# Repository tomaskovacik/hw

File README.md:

repo for hw(pcbs mainly) part of electronic projects, sometimes there is also few software files here:)

kicad: projects made in kicad

audi_chorus_cd_changer_input: all files needed to convert audi chorus 1 to enable CD changer input, more: http://kovo-blog.blogspot.sk/2013/11/how-to-enable-cd-changer-input-on-audi.html

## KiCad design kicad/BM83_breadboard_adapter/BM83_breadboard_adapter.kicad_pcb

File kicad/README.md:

schematics and PCBs made in kicad

arduino based cdc emulator moved to https://github.com/tomaskovacik/vwcdavr/tree/master/HW/arduino_based_cdc_emulator

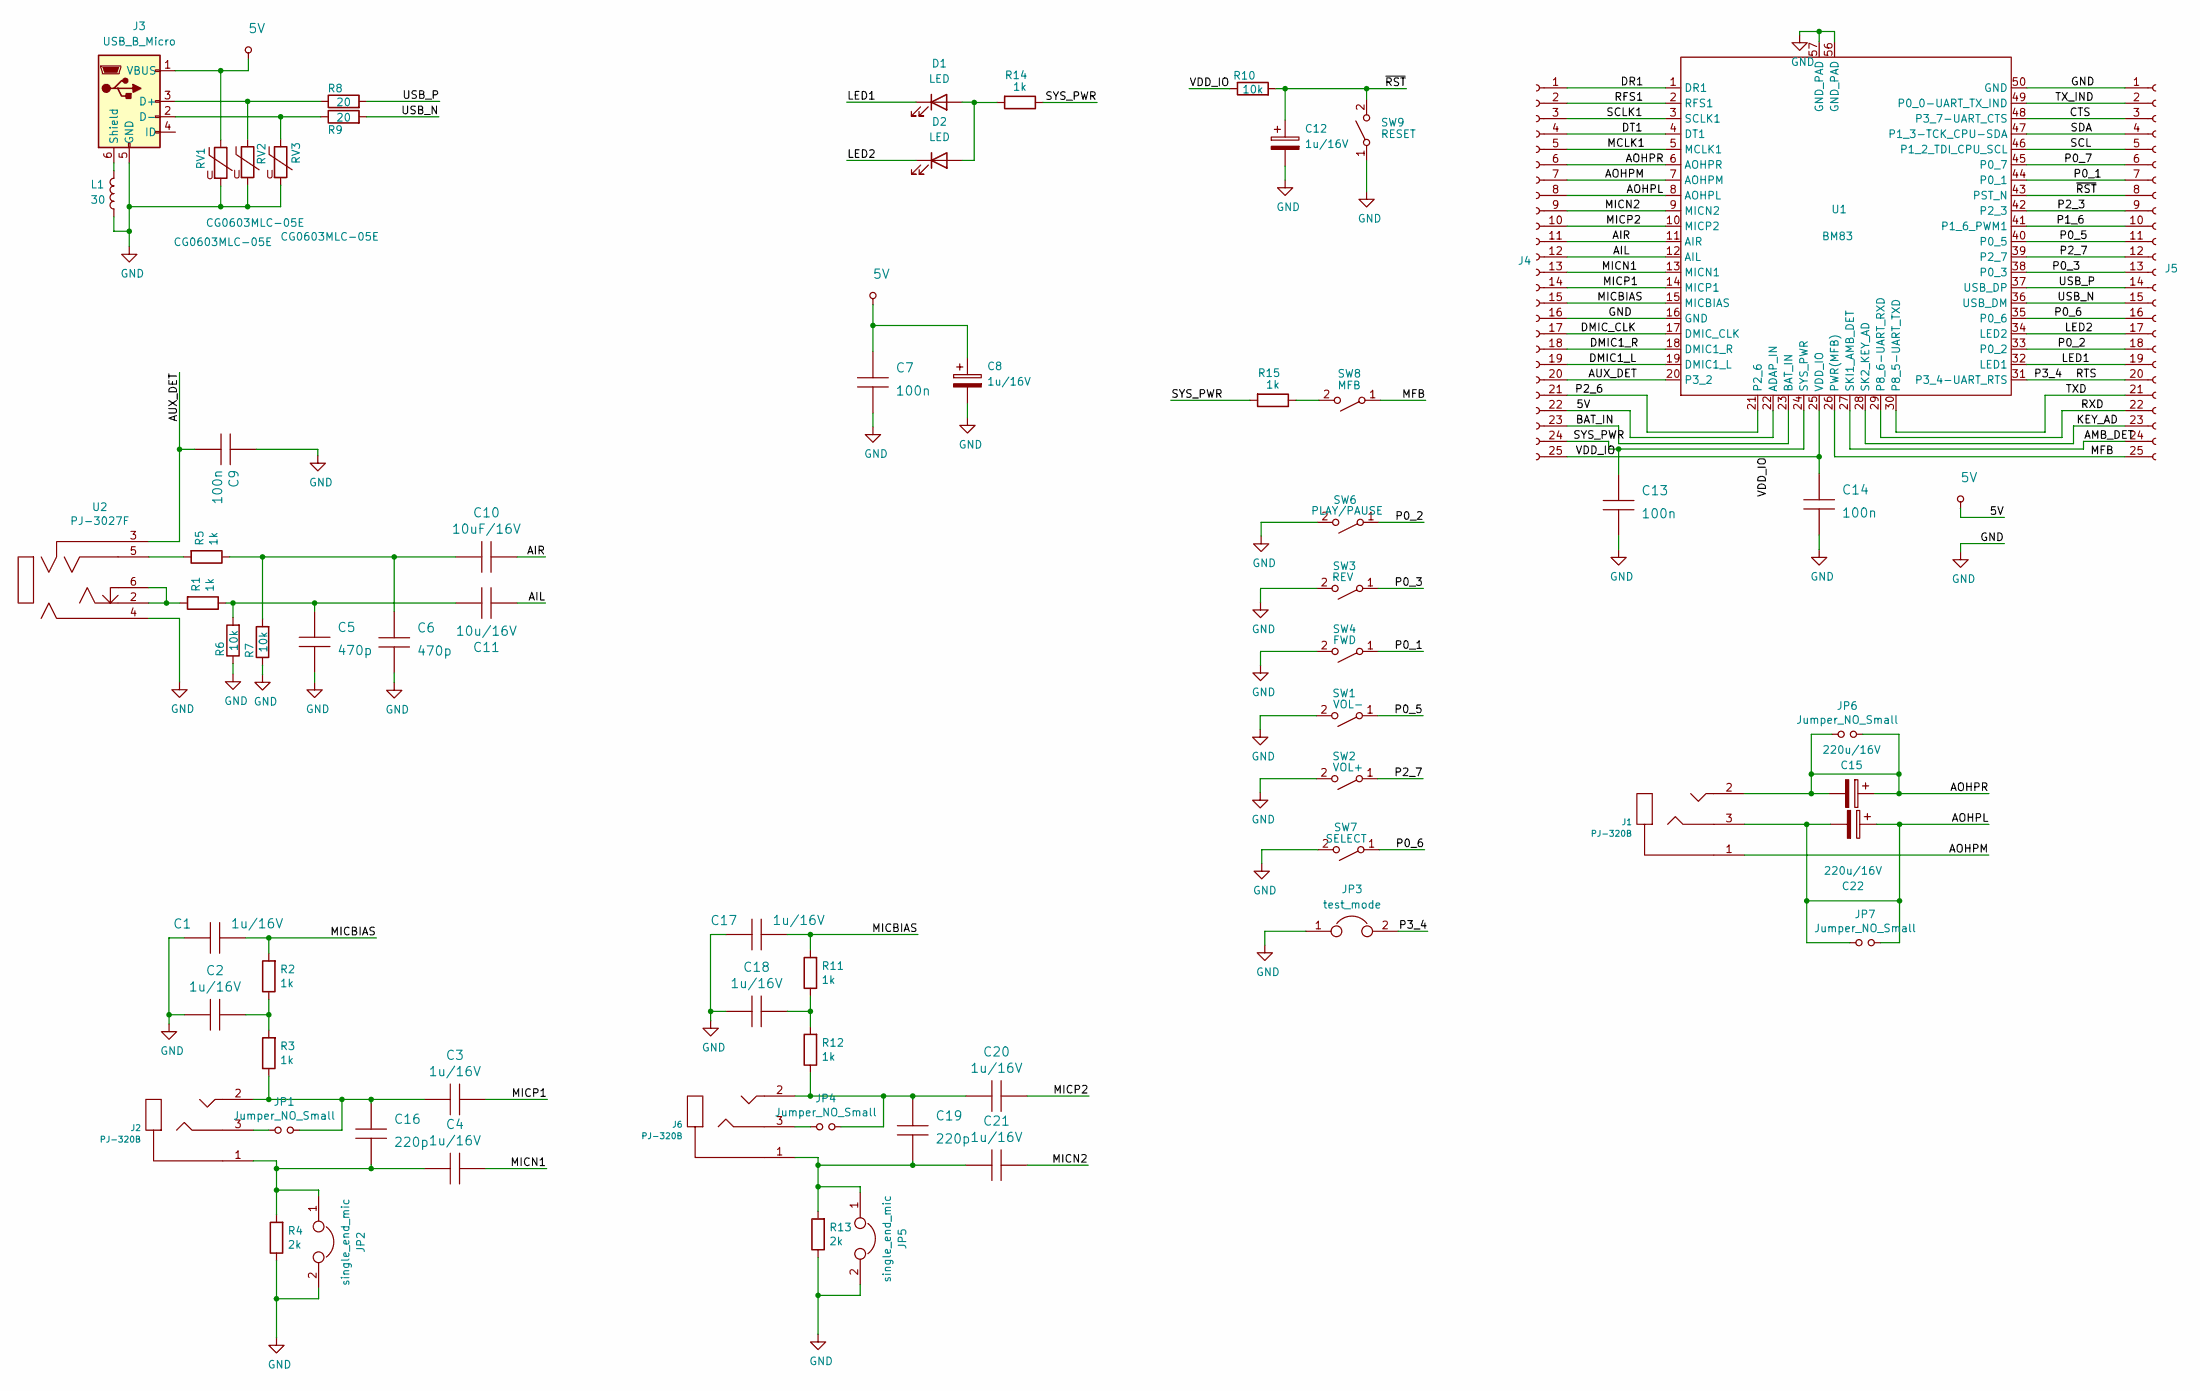
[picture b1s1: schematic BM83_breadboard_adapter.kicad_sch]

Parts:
C1, C2, C3, C4, C17, C18, C20, C21: 1u/16V; C_1206_HandSoldering
C5, C6: 470p; C_0805_HandSoldering
C7, C9, C13, C14: 100n; C_0805_HandSoldering
C8, C12: 1u/16V; TantalC_SizeA_EIA-3216_HandSoldering
C10: 10uF/16V; C_1206_HandSoldering
C11: 10u/16V; C_1206_HandSoldering
C15, C22: 220u/16V; C_Radial_D6.3_L11.2_P2.5
C16, C19: 220p; C_0805_HandSoldering
D1, D2: LED; LED_1206_HandSoldering
J1, J2, J6: PJ-320B; 3.5mm_stereo_jack_PJ320B
J3: USB_B_Micro; USB_Micro-B
J4, J5: Conn_01x25_Female; Pin_Header_Straight_1x25
JP1, JP4, JP6, JP7: Jumper_NO_Small; SolderJumper-2_P1.3mm_Open_RoundedPad1.0x1.5mm
JP2, JP5: single_end_mic; SolderJumper-2_P1.3mm_Open_RoundedPad1.0x1.5mm
JP3: test_mode; Pin_Header_Straight_1x02
L1: 30; R_1206_HandSoldering
R1, R2, R3, R5, R11, R12, R14, R15: 1k; R_0805_HandSoldering
R4, R13: 2k; R_0805_HandSoldering
R6, R7, R10: 10k; R_0805_HandSoldering
R8, R9: 20; R_0805_HandSoldering
RV1, RV2, RV3: CG0603MLC-05E; R_0603_HandSoldering
SW1: VOL-; SW_SPST_FSMSM
SW2: VOL+; SW_SPST_FSMSM
SW3: REV; SW_SPST_FSMSM
SW4: FWD; SW_SPST_FSMSM
SW6: PLAY/PAUSE; SW_SPST_FSMSM
SW7: SELECT; SW_SPST_FSMSM
SW8: MFB; SW_SPST_FSMSM
SW9: RESET; SW_SPST_FSMSM
U1: BM83
U2: PJ-3027F; PJ-327A

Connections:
5V: C7.1, C8.1, J3.1 (VBUS), J4.22, RV1.1, U1.22 (ADAP_IN)
/AIL: C11.2, J4.12, U1.12 (AIL)
/AIR: C10.1, J4.11, U1.11 (AIR)
/AMB_DET: J5.24, U1.27 (SKI1_AMB_DET)
/AOHPL: C22.1, C22.2, J1.3, J4.8, JP7.1, JP7.2, U1.8 (AOHPL)
/AOHPM: J1.1, J4.7, U1.7 (AOHPM)
/AOHPR: C15.1, C15.2, J1.2, J4.6, JP6.1, JP6.2, U1.6 (AOHPR)
/AUX_DET: C9.2, J4.20, U1.20 (P3_2), U2.3
/BAT_IN: J4.23, U1.23 (BAT_IN)
/CTS: J5.3, U1.48 (P3_7-UART_CTS)
/DMIC1_L: J4.19, U1.19 (DMIC1_L)
/DMIC1_R: J4.18, U1.18 (DMIC1_R)
/DMIC_CLK: J4.17, U1.17 (DMIC_CLK)
/DR1: J4.1, U1.1 (DR1)
/DT1: J4.4, U1.4 (DT1)
/KEY_AD: J5.23, U1.28 (SK2_KEY_AD)
/LED1: D1.1 (K), J5.19, U1.32 (LED1)
/LED2: D2.1 (K), J5.17, U1.34 (LED2)
/MCLK1: J4.5, U1.5 (MCLK1)
/MFB: J5.25, SW8.1 (A), U1.26 (PWR(MFB))
/MICBIAS: C1.1, C17.1, J4.15, R2.2, R11.2, U1.15 (MICBIAS)
/MICN1: C4.1, J4.13, U1.13 (MICN1)
/MICN2: C21.1, J4.9, U1.9 (MICN2)
/MICP1: C3.1, J4.14, U1.14 (MICP1)
/MICP2: C20.1, J4.10, U1.10 (MICP2)
/P0_1: J5.7, SW4.1 (A), U1.44 (P0_1)
/P0_2: J5.18, SW6.1 (A), U1.33 (P0_2)
/P0_3: J5.13, SW3.1 (A), U1.38 (P0_3)
/P0_5: J5.11, SW1.1 (A), U1.40 (P0_5)
/P0_6: J5.16, SW7.1 (A), U1.35 (P0_6)
/P0_7: J5.6, U1.45 (P0_7)
/P1_6: J5.10, U1.41 (P1_6_PWM1)
/P2_3: J5.9, U1.42 (P2_3)
/P2_6: J4.21, U1.21 (P2_6)
/P2_7: J5.12, SW2.1 (A), U1.39 (P2_7)
/P3_4: J5.20, JP3.2, U1.31 (P3_4-UART_RTS)
/RFS1: J4.2, U1.2 (RFS1)
/RXD: J5.22, U1.29 (P8_6-UART_RXD)
/SCL: J5.5, U1.46 (P1_2_TDI_CPU_SCL)
/SCLK1: J4.3, U1.3 (SCLK1)
/SDA: J5.4, U1.47 (P1_3-TCK_CPU-SDA)
/SYS_PWR: C13.1, J4.24, R14.1, R15.2, U1.24 (SYS_PWR)
/TXD: J5.21, U1.30 (P8_5-UART_TXD)
/TX_IND: J5.2, U1.49 (P0_0-UART_TX_IND)
/USB_N: J5.15, R9.2, U1.36 (USB_DM)
/USB_P: J5.14, R8.2, U1.37 (USB_DP)
/VDD_IO: C14.1, J4.25, R10.1, U1.25 (VDD_IO)
/~RST: C12.1, J5.8, R10.2, SW9.2 (B), U1.43 (PST_N)
GND: C1.2, C2.2, C5.2, C6.2, C7.2, C8.2, C9.1, C12.2, C13.2, C14.2, C17.2, C18.2, J3.5 (GND), J4.16, J5.1, JP2.2, JP3.1, JP5.2, L1.1, R4.1, R6.1, R7.1, R13.1, RV1.2, RV2.2, RV3.2, SW1.2 (B), SW2.2 (B), SW3.2 (B), SW4.2 (B), SW6.2 (B), SW7.2 (B), SW9.1 (A), U1.16 (GND), U1.50 (GND), U1.56 (GND_PAD), U1.57 (GND_PAD), U2.4
unnamed: C2.1, R2.1, R3.2
unnamed: C6.1, C10.2, R5.1, R7.2
unnamed: C5.1, C11.1, R1.1, R6.2
unnamed: C3.2, C16.1, J2.2, JP1.2, R3.1
unnamed: C4.2, C16.2, J2.1, JP2.1, R4.2
unnamed: C18.1, R11.1, R12.2
unnamed: C19.1, C20.2, J6.2, JP4.2, R12.1
unnamed: C19.2, C21.2, J6.1, JP5.1, R13.2
unnamed: D1.2 (A), D2.2 (A), R14.2
unnamed: J2.3, JP1.1
unnamed: J3.2 (D-), R9.1, RV3.1
unnamed: J3.3 (D+), R8.1, RV2.1
unnamed: J3.6 (Shield), L1.2
unnamed: J6.3, JP4.1
unnamed: R1.2, U2.2, U2.6
unnamed: R5.2, U2.5
unnamed: R15.1, SW8.2 (B)

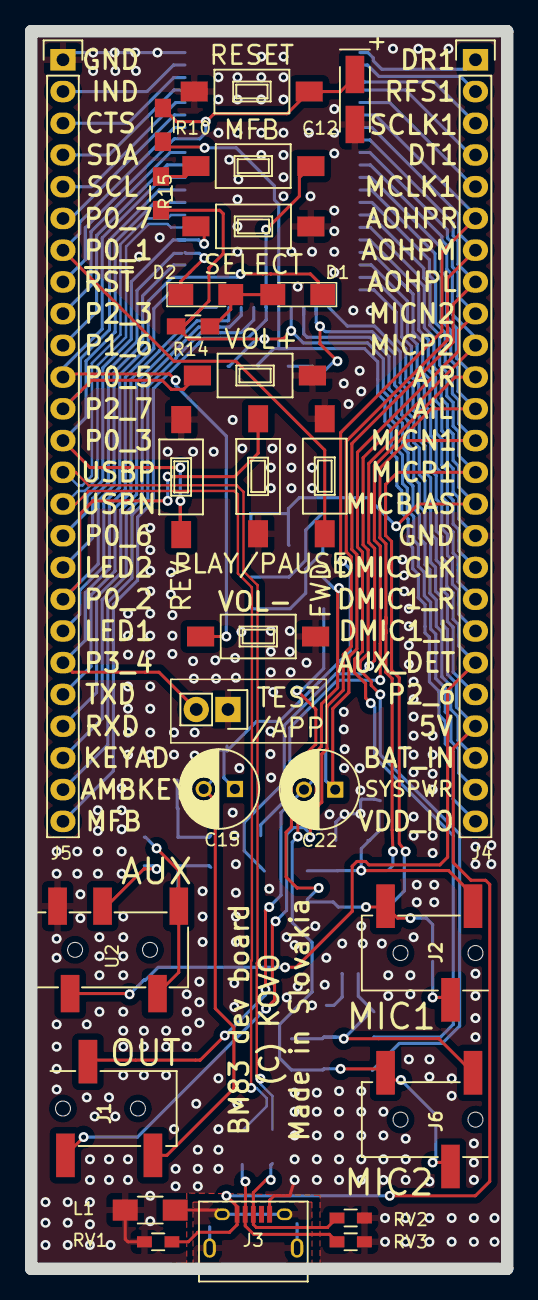
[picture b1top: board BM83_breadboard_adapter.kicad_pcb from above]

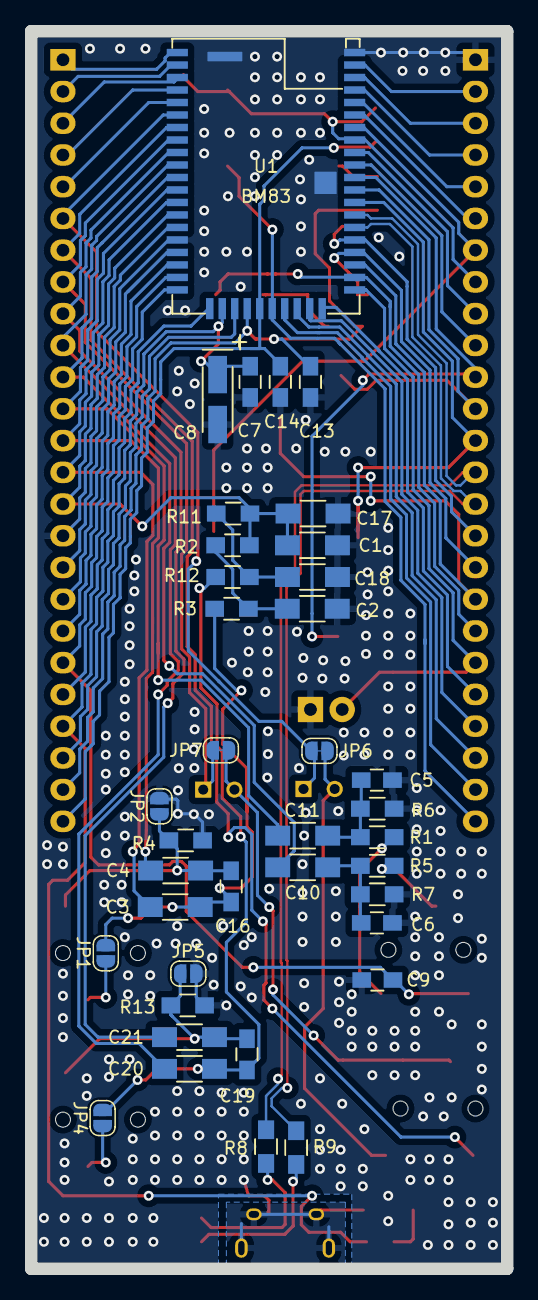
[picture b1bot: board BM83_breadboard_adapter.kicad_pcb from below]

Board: 2 copper layers, 38.1 x 99.1 mm, 66 parts (38 on the bottom side), 66 nets.

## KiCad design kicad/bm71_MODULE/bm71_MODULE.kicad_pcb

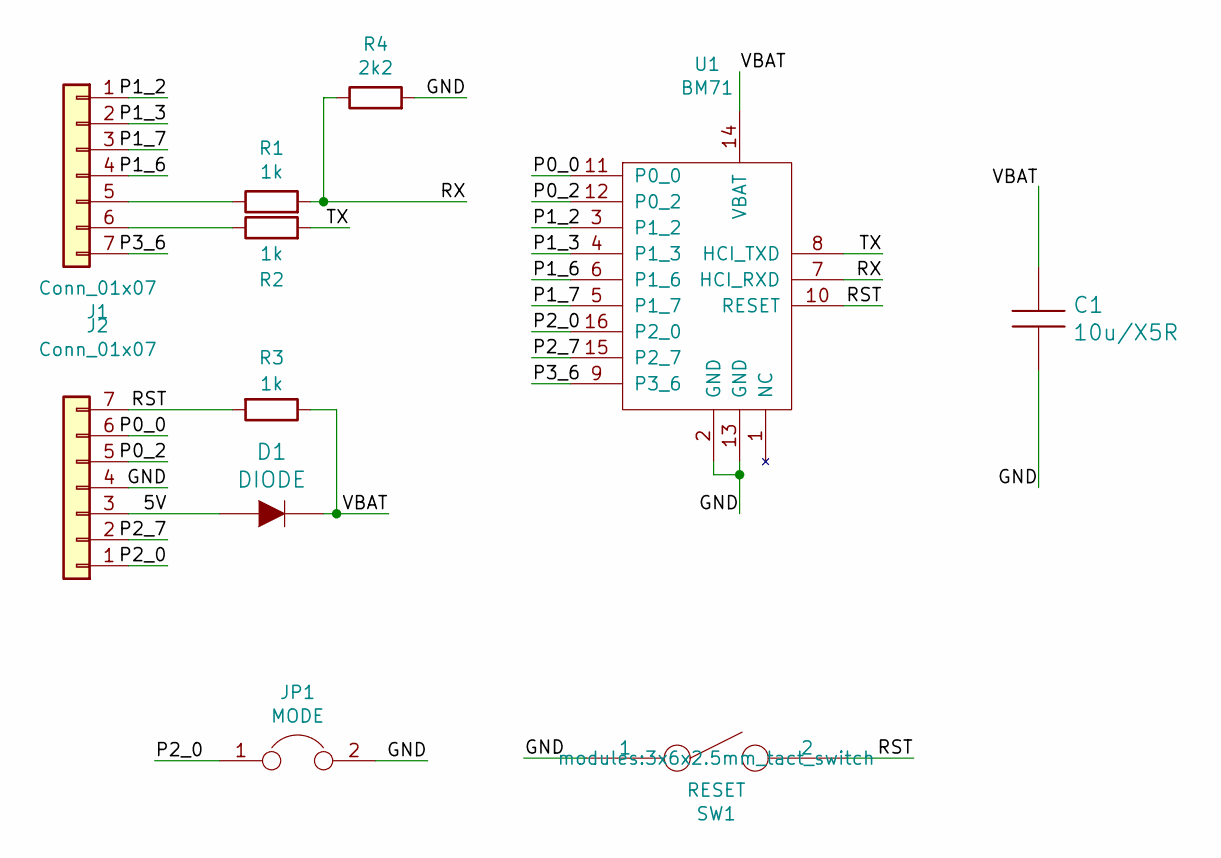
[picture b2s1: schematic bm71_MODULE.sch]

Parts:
C1: 10u/X5R; C_1206_HandSoldering
D1: DIODE; D_MicroMELF_Hadsoldering
J1, J2: Conn_01x07; Pin_Header_Straight_1x07
JP1: MODE; Pin_Header_Straight_1x02
R1, R2, R3: 1k; R_0805_HandSoldering
R4: 2k2; R_0805_HandSoldering
SW1: RESET; 3x6x2.5mm_tact_switch
U1: BM71

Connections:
/5V: D1.1 (A), J2.3
/GND: C1.2, J2.4, JP1.2, R4.2, SW1.1, U1.2 (GND), U1.13 (GND)
/P0_0: J2.6, U1.11 (P0_0)
/P0_2: J2.5, U1.12 (P0_2)
/P1_2: J1.1, U1.3 (P1_2)
/P1_3: J1.2, U1.4 (P1_3)
/P1_6: J1.4, U1.6 (P1_6)
/P1_7: J1.3, U1.5 (P1_7)
/P2_0: J2.1, JP1.1, U1.16 (P2_0)
/P2_7: J2.2, U1.15 (P2_7)
/P3_6: J1.7, U1.9 (P3_6)
/RST: J2.7, R3.2, SW1.2, U1.10 (RESET)
/RX: R1.2, R4.1, U1.7 (HCI_RXD)
/TX: R2.2, U1.8 (HCI_TXD)
/VBAT: C1.1, D1.2 (K), R3.1, U1.14 (VBAT)
unnamed: J1.5, R1.1
unnamed: J1.6, R2.1

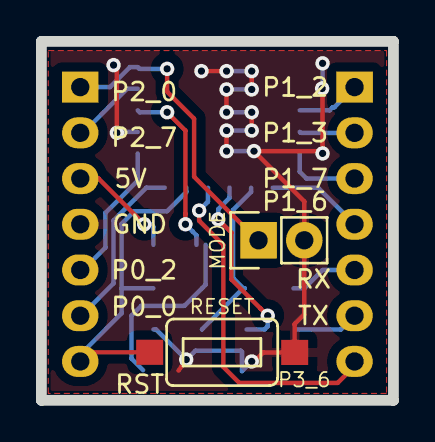
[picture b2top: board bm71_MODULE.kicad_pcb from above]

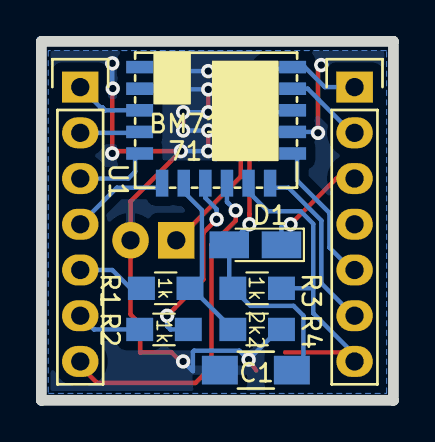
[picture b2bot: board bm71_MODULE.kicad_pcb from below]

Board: 2 copper layers, 19.6 x 19.9 mm, 11 parts (9 on the bottom side), 17 nets.

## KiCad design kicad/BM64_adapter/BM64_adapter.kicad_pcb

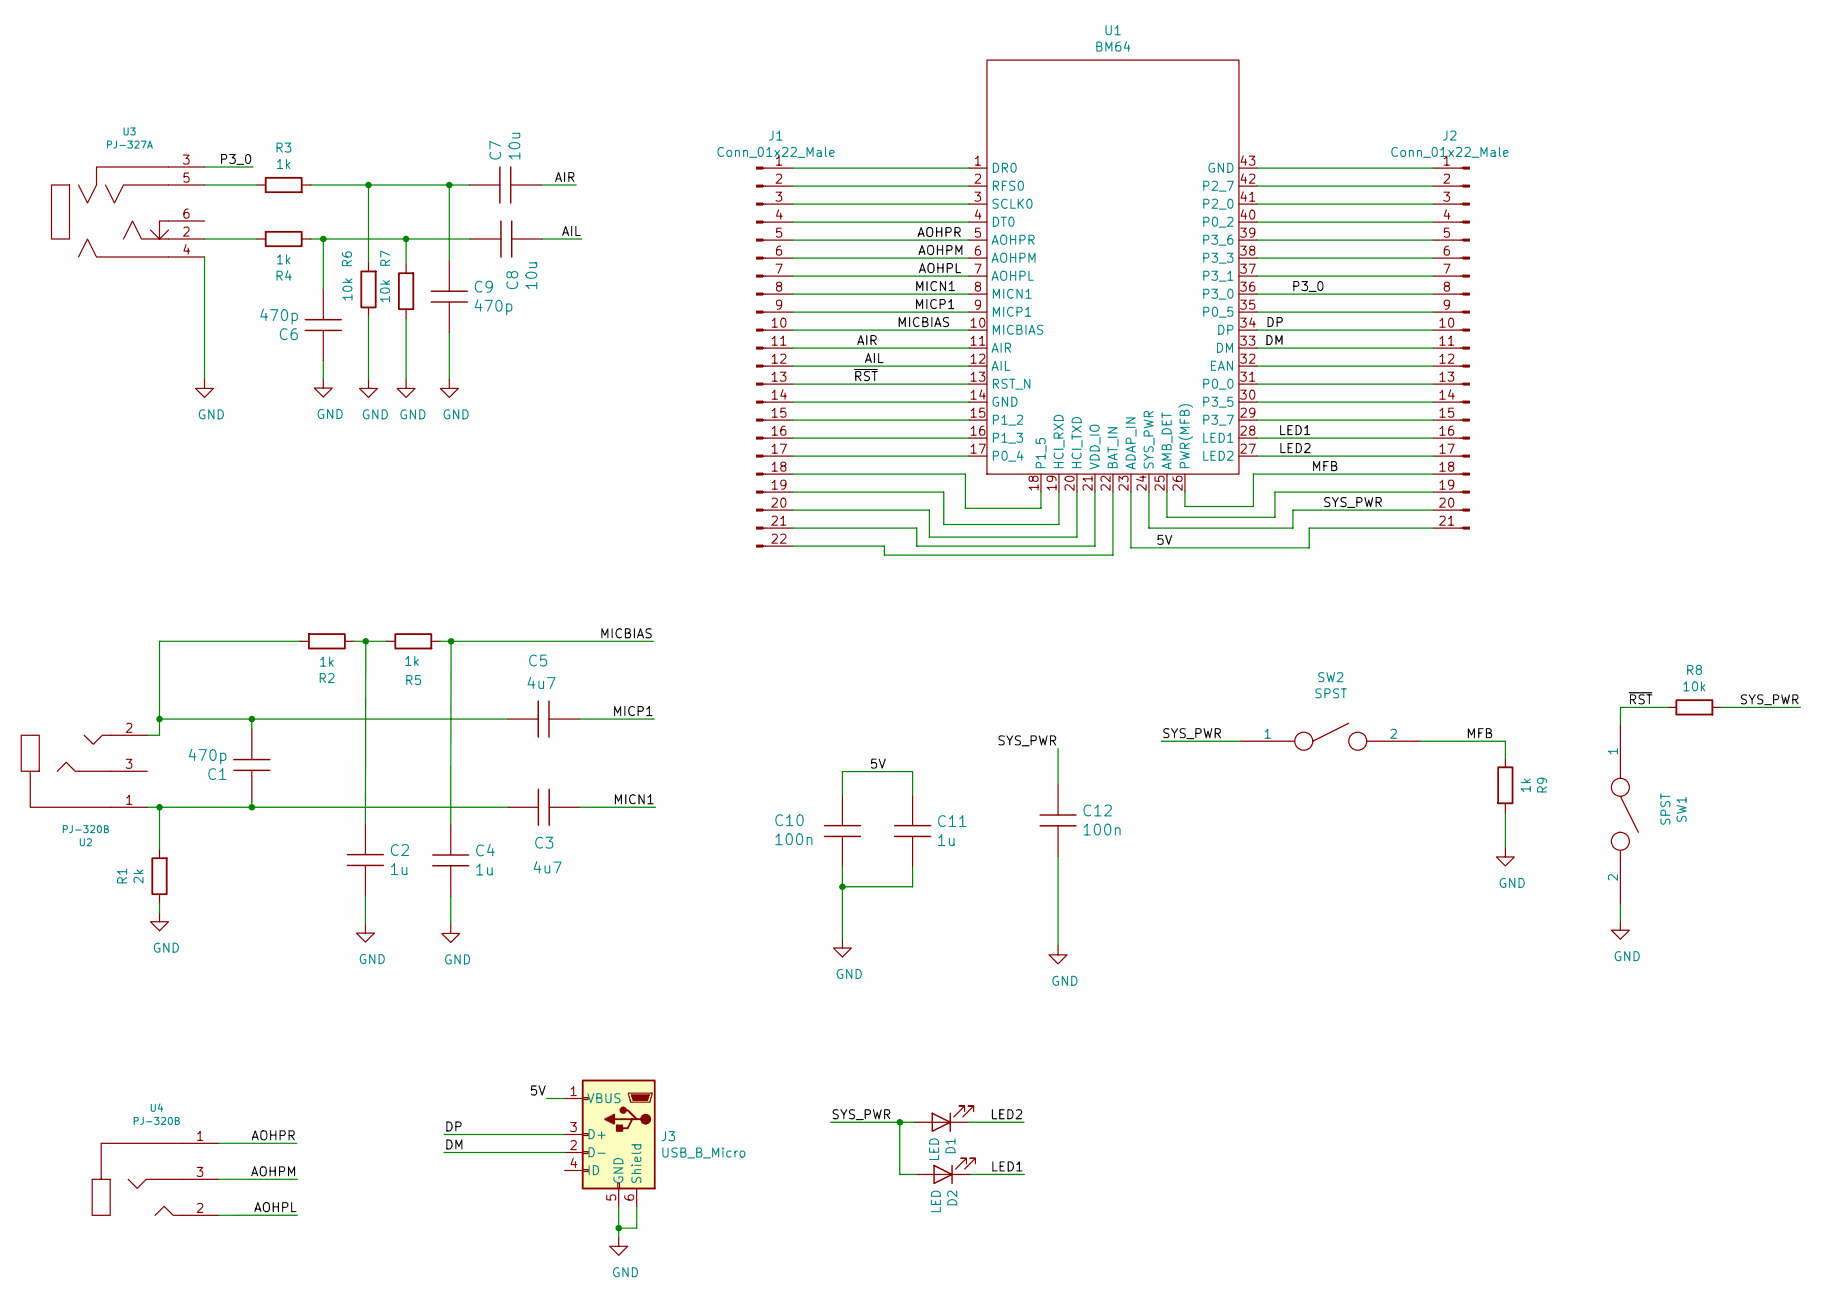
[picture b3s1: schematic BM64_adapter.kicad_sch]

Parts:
C1, C6, C9: 470p; C_1206_HandSoldering
C2, C4, C11: 1u; C_1206_HandSoldering
C3, C5: 4u7; C_1206_HandSoldering
C7, C8: 10u; C_1206_HandSoldering
C10, C12: 100n; C_1206_HandSoldering
D1, D2: LED; LED_1206_HandSoldering
J1: Conn_01x22_Male; Pin_Header_Straight_1x22_Pitch2.54mm
J2: Conn_01x22_Male; Pin_Header_Straight_1x21_Pitch2.54mm
J3: USB_B_Micro; USB_Micro-B
R1: 2k; R_0805_HandSoldering
R2, R3, R4, R5, R9: 1k; R_0805_HandSoldering
R6, R7, R8: 10k; R_0805_HandSoldering
SW1, SW2: SPST; 3x6x2.5mm_tact_switch
U1: BM64
U2, U4: PJ-320B; 3.5mm_stereo_jack_PJ320B
U3: PJ-327A

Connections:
/5V: C10.1, C11.1, J2.21, J3.1 (VBUS), U1.23 (ADAP_IN)
/AIL: C8.2, J1.12, U1.12 (AIL)
/AIR: C7.2, J1.11, U1.11 (AIR)
/AOHPL: J1.7, U1.7 (AOHPL), U4.2
/DM: J2.11, J3.2 (D-), U1.33 (DM)
/DP: J2.10, J3.3 (D+), U1.34 (DP)
/LED1: D2.1 (K), J2.16, U1.28 (LED1)
/LED2: D1.1 (K), J2.17, U1.27 (LED2)
/MFB: J2.18, R9.1, SW2.2, U1.26 (PWR(MFB))
/MICBIAS: C4.1, J1.10, R5.2, U1.10 (MICBIAS)
/MICN1: C3.2, J1.8, U1.8 (MICN1)
/MICP1: C5.2, J1.9, U1.9 (MICP1)
/P3_0: J2.8, U1.36 (P3_0), U3.3
/SYS_PWR: C12.1, D1.2 (A), D2.2 (A), J2.20, R8.2, SW2.1, U1.24 (SYS_PWR)
/~RST: J1.13, R8.1, SW1.1, U1.13 (RST_N)
GND: C2.2, C4.2, C6.1, C9.2, C10.2, C11.2, C12.2, J3.5 (GND), J3.6 (Shield), R1.1, R6.1, R7.1, R9.2, SW1.2, U3.4
unnamed: C1.1, C3.1, R1.2, U2.1
unnamed: C1.2, C5.1, R2.2, U2.2
unnamed: C2.1, R2.1, R5.1
unnamed: C6.2, C8.1, R4.1, R7.2
unnamed: C7.1, C9.1, R3.2, R6.2
unnamed: J1.1, U1.1 (DR0)
unnamed: J1.2, U1.2 (RFS0)
unnamed: J1.3, U1.3 (SCLK0)
unnamed: J1.4, U1.4 (DT0)
unnamed: J1.14, U1.14 (GND)
unnamed: J1.15, U1.15 (P1_2)
unnamed: J1.16, U1.16 (P1_3)
unnamed: J1.17, U1.17 (P0_4)
unnamed: J1.18, U1.18 (P1_5)
unnamed: J1.19, U1.19 (HCI_RXD)
unnamed: J1.20, U1.20 (HCI_TXD)
unnamed: J1.21, U1.21 (VDD_IO)
unnamed: J1.22, U1.22 (BAT_IN)
unnamed: J2.1, U1.43 (GND)
unnamed: J2.2, U1.42 (P2_7)
unnamed: J2.3, U1.41 (P2_0)
unnamed: J2.4, U1.40 (P0_2)
unnamed: J2.5, U1.39 (P3_6)
unnamed: J2.6, U1.38 (P3_3)
unnamed: J2.7, U1.37 (P3_1)
unnamed: J2.9, U1.35 (P0_5)
unnamed: J2.12, U1.32 (EAN)
unnamed: J2.13, U1.31 (P0_0)
unnamed: J2.14, U1.30 (P3_5)
unnamed: J2.15, U1.29 (P3_7)
unnamed: J2.19, U1.25 (AMB_DET)
unnamed: R3.1, U3.5
unnamed: R4.2, U3.2

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
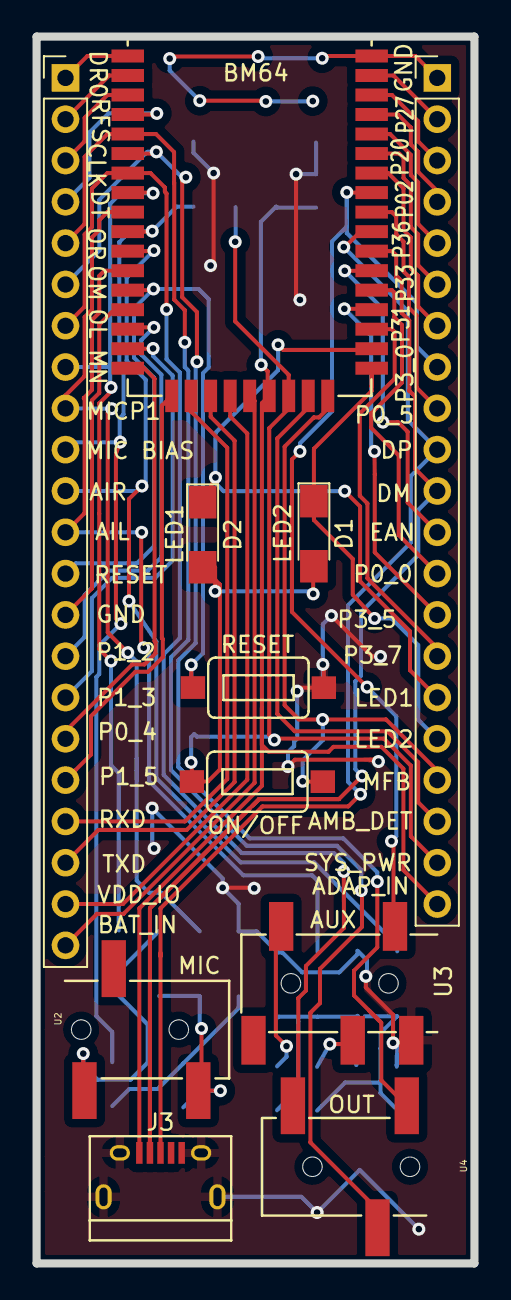
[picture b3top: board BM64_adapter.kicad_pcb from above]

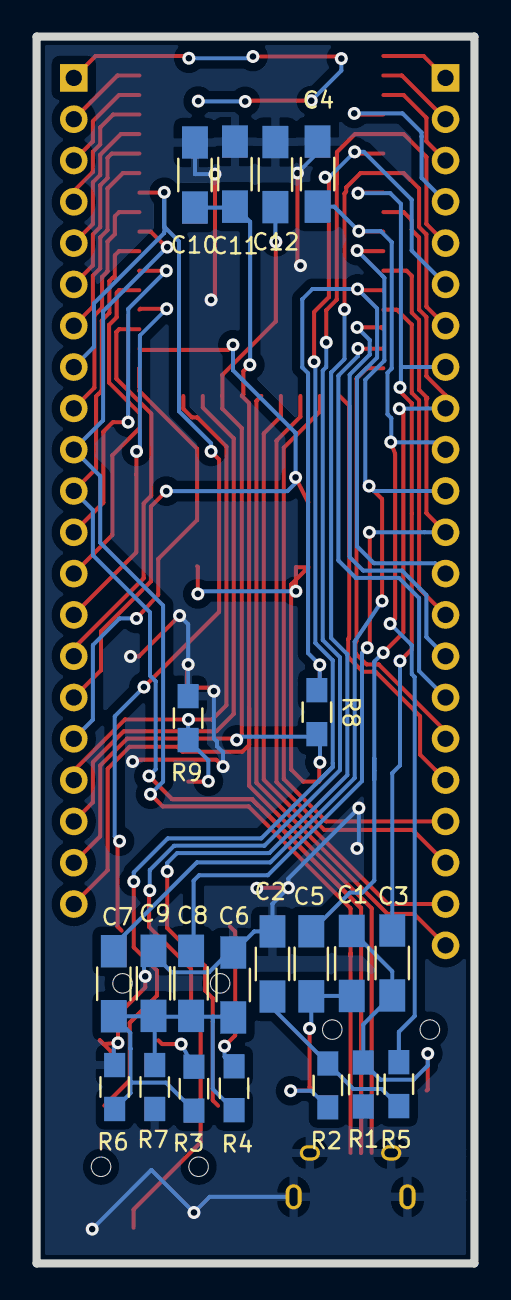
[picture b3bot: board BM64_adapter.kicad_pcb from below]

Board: 2 copper layers, 26.9 x 75.4 mm, 32 parts (21 on the bottom side), 51 nets.

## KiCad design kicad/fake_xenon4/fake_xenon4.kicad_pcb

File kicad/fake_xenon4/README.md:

HW for fake headlights autoleveling

SW is here: https://github.com/tomaskovacik/arduino/tree/master/fake_xenon_adjuster

you can buy set of 2 here:

https://www.tindie.com/products/tomaskovacik/adapter-for-fxr-40-audi-a4-b5/

or here:

https://www.tindie.com/products/tomaskovacik/template-for-4tl-r-bixenon-depo-audi-a4-b5-lights/

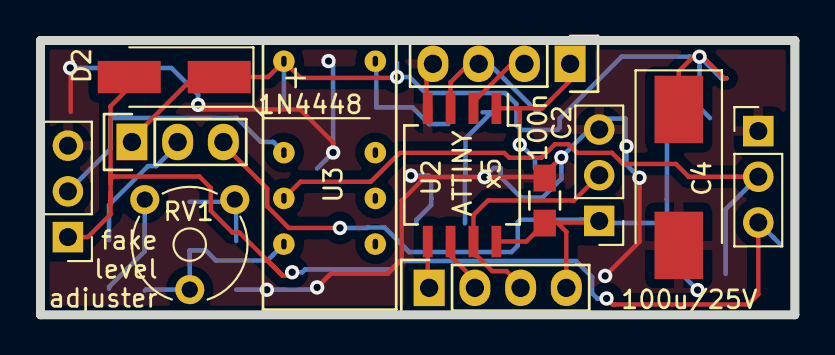
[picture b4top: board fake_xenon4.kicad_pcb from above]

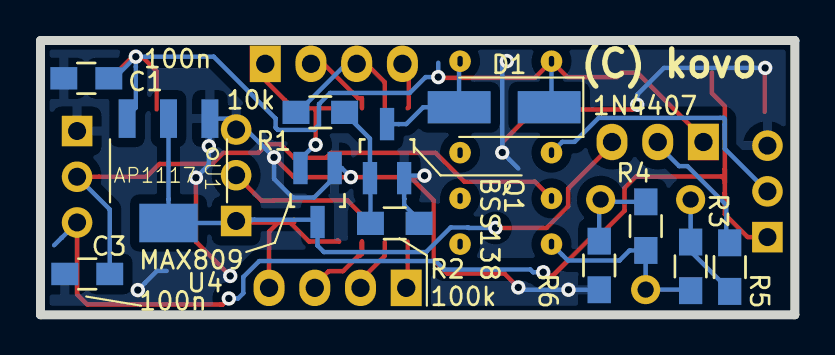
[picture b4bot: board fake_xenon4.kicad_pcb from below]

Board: 2 copper layers, 41.9 x 15.2 mm, 24 parts (12 on the bottom side), 18 nets.

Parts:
C1, C2, C3: 100n; C_0805_HandSoldering
C4: 100u/25V; CP_Tantalum_Case-D_EIA-7343-31_Hand
D1: 1N4407; D_SMA_Handsoldering
D2: 1N4448; D_SMA_Handsoldering
J1, J2: Conn_01x03_Male; Pin_Header_Straight_1x03_Pitch2.54mm
J3, J4: Conn_01x04_Female; Pin_Header_Straight_1x04
JP1: Jumper_3_Bridged12; Pin_Header_Straight_1x03_Pitch2.54mm
JP2: Jumper_3_Bridged12; Pin_Header_Straight_1x03
Q1: BSS138; SOT-23_Handsoldering
R1: 10k; R_0805_HandSoldering
R2: 100k; R_0805_HandSoldering
R3, R4, R5, R6: R; R_0805_HandSoldering
RV1: R_POT; Potentiometer_Trimmer_Piher_PT-6v_Horizontal
U1: AP1117; AB2_SOT223
U2: ATtiny25-20PU; SO-8_5.3x6.2mm_Pitch1.27mm
U3: Fujitsu_NA-Series; FUJITSU-NA-SERIES
U4: MAX809; SOT-23_Handsoldering

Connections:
5V: C2.1, J3.4, JP1.1, JP2.3, U1.2, U2.8, U4.3
+12V: C1.1, C4.1, D1.1, D2.1, JP2.1, U1.3, U3.1
+12VA: D2.2, J1.1, J2.3
/RESET: J4.1, U2.1, U4.2
GND: C1.2, C2.2, C3.2, C4.2, J1.3, J2.1, J4.4, JP1.3, Q1.2, R2.1, R6.1, U1.1, U2.4, U4.1
unnamed: C3.1, J2.2, U3.4
unnamed: D1.2, Q1.3, U3.12
unnamed: J1.2, U3.3
unnamed: J3.1, U2.5
unnamed: J3.2, U2.6
unnamed: J3.3, JP1.2, U2.7
unnamed: J4.2, U2.2
unnamed: J4.3, R1.2, U2.3
unnamed: JP2.2, R5.2
unnamed: Q1.1, R1.1, R2.2
unnamed: R3.1, R4.2, RV1.2, U3.5
unnamed: R3.2, R5.1, RV1.1
unnamed: R4.1, R6.2, RV1.3

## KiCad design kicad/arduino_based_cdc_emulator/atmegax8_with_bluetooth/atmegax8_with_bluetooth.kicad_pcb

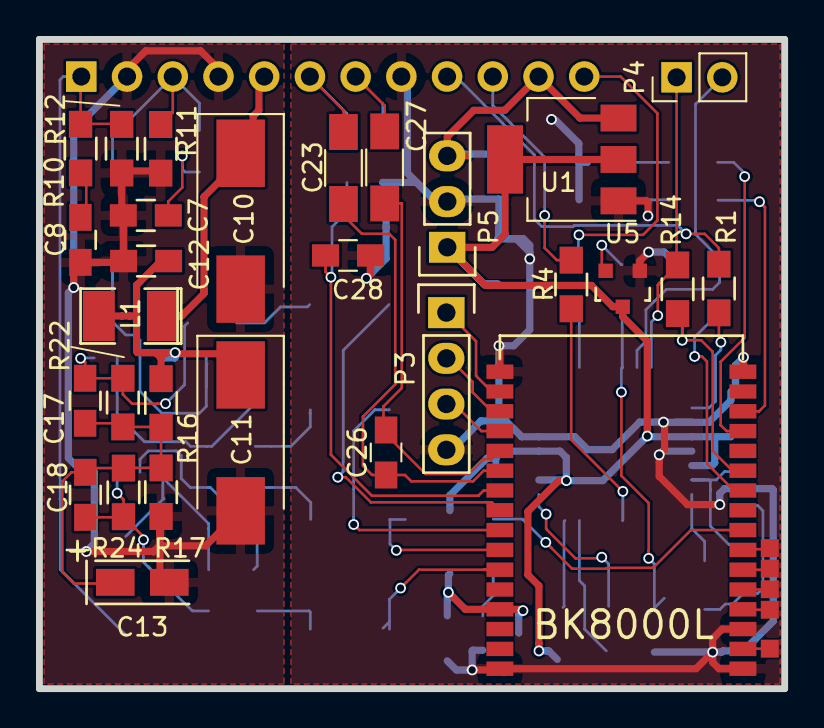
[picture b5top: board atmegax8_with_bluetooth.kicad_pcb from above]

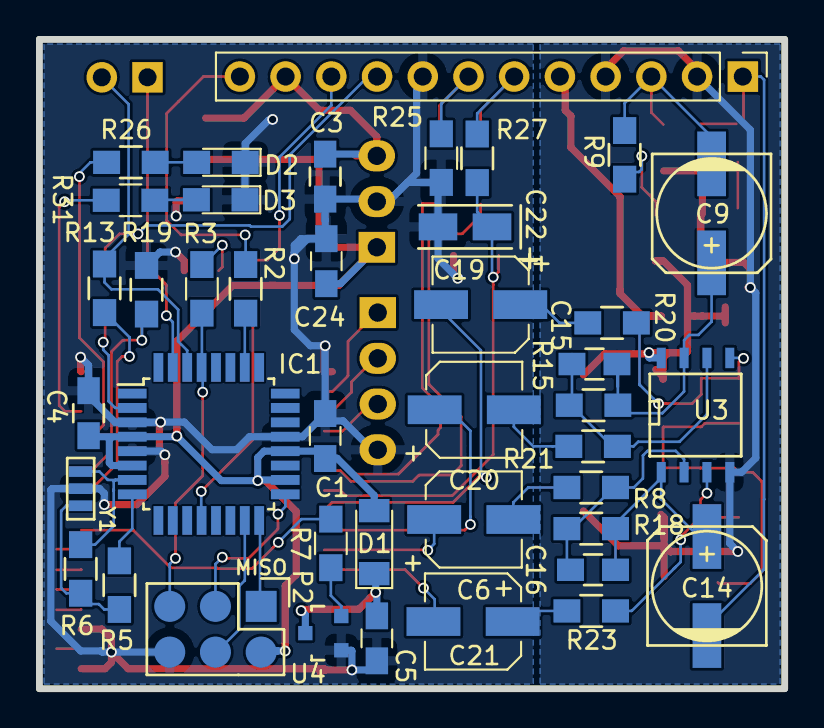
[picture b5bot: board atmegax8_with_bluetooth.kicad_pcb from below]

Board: 2 copper layers, 41.4 x 36.1 mm, 75 parts (41 on the bottom side), 63 nets.

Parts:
C1, C3, C4, C5, C7, C8, C12, C24, C28: 100n; C_0805_HandSoldering
C6, C19, C20, C21: 1m/16V; CP_Elec_5x5.8
C9, C14: 4.7m/25V; c_elec_6.3x5.7
C10, C11: 100u/16V; CP_Tantalum_Case-D_EIA-7343-31_Hand
C13, C22: 4u7/10V; TantalC_SizeA_EIA-3216_Wave
C15, C16, C17, C18: 33p; C_0805_HandSoldering
C23, C27: 1u/10V; C_1206_HandSoldering
C26: 10n; C_0805_HandSoldering
D1: 1N4148; D_MiniMELF
D2, D3: LED; LED_0805_HandSoldering
IC1: ATMEGA88-A; TQFP-32_7x7mm_Pitch0.8mm
J1: Ant; 1pin_smd
J2: TMS; 1pin_smd
J3: TCK; 1pin_smd
J4: TDO; 1pin_smd
J5: TDI; 1pin_smd
L1: 330u; SMD-1210_Pol
P1: CONN_10; Pin_Header_Straight_1x12_Pitch2.54mm
P2: SPI; Pin_Header_Straight_2x03
P3: CONN_4; Pin_Header_Straight_1x04
P4: SERIAL; Pin_Header_Straight_1x02_Pitch2.54mm
P5: CONN_4; Pin_Header_Straight_1x03
R1, R2, R3, R4, R7, R13, R14, R25, R26, R27, R31: 1k; R_0805_HandSoldering
R5: 100; R_0805_HandSoldering
R6: 1M; R_0805_HandSoldering
R8, R20, R21, R23: 22k; R_0805_HandSoldering
R9, R10: 39R; R_0805_HandSoldering
R11, R12, R15, R18, R22, R24: 47k; R_0805_HandSoldering
R16, R17: 100k; R_0805_HandSoldering
R19: 2k; R_0805_HandSoldering
U1: AP1117; SOT-223-3_TabPin2
U2: F-6188; F-6188_nosilk
U3: TL072; SOIC-8-N
U4, U5: MAX809; SOT-23
Y1: 16MHz; MURATA_CSTCE_V53

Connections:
+5V: C1.1, C4.1, C24.1, D1.2 (A), IC1.4 (VCC), IC1.6 (VCC), IC1.18 (AVCC), IC1.20 (AREF), P2.2, P5.1, U1.2 (VOUT), U5.3 (VCC)
+12C: C11.1, C12.1, L1.2, R16.2, U3.8 (V+)
+12V: C10.1, L1.1, P1.5
+BATT: C5.1, D1.1 (K), U2.29 (VBAT), U4.3 (VCC)
/AOUTL: C14.2, P1.1, R10.2, R12.2
/AOUTR: C9.2, P1.3, R9.2, R11.2
/ARESET: IC1.29 ((PCINT14/~RESET~)PC6), P2.5, R3.2
/BTOUTL: C20.1, U2.25 (AUDIO_LP)
/BTOUTLN: C19.2, U2.24 (AUDIO_LN)
/BTOUTR: C6.1, U2.26 (AUDIO_RP)
/BTOUTRN: C21.2, U2.27 (AUDIO_RN)
/BT_RESET: R7.2, U2.8 (RSTN)
/CDC_ENA_12V: C3.1, P1.11, P5.3, U1.3 (VIN)
/Clock: IC1.2 ((PCINT20/XCK/T0)PD4), R1.2
/DataIn: IC1.26 ((PCINT11/ADC3)PC3), R2.2
/DataOut: P1.10, R4.2
/INL: P3.3, U2.20 (AUX_INL)
/INR: P3.2, U2.19 (AUX_INR)
/IN_DETECT: P3.1, U2.18 (AUXDET/GPIO11)
/LED1: R26.1, U2.13 (LED0/GPIO3)
/LED2: R31.1, U2.14 (LED1/GPIO4)
/MICN: C26.2, C27.1, U2.21 (MICN)
/MICP: C23.1, C26.1, U2.22 (MICP)
/MIC_BIAS: C22.1, C28.1, R27.2, U2.23 (MIC_BIAS)
/MIC_IN1: C27.2, P1.7, R25.2
/MIC_IN2: C23.2, P1.6, R27.1
/MISO: IC1.16 ((PCINT4/MISO)PB4), P2.1
/MOSI: IC1.15 ((PCINT3/OC2/MOSI)PB3), P2.4
/SCK: IC1.17 ((PCINT5/SCK)PB5), P2.3
/VGND: C13.1, C17.2, C18.2, R16.1, R17.2, R22.1, R24.1
GND: C1.2, C3.2, C4.2, C5.2, C22.2, C24.2, C28.2, D2.1 (K), D3.1 (K), IC1.3 (GND), IC1.5 (GND), IC1.21 (GND), P1.8, P2.6, P3.4, P5.2, R19.2, R25.1, U1.1 (ADJ/GND), U2.1 (GND), U2.3 (GND), U2.16 (GND), U2.17 (GND), U2.32 (GND), U4.1 (GND), U5.1 (GND), Y1.2
GNDA: C7.2, C8.2, C10.2, C11.2, C12.2, C13.2, P1.2, P1.4, R11.1, R12.1, R17.1, U3.4 (V-)
unnamed: C6.2, R8.2
unnamed: C7.1, R9.1
unnamed: C8.1, R10.1
unnamed: C14.1, C16.1, R18.2, U3.1
unnamed: C9.1, C15.1, R15.2, U3.7
unnamed: C15.2, R15.1, R21.1, U3.6 (-)
unnamed: C16.2, R8.1, R18.1, U3.2 (-)
unnamed: C17.1, R20.2, R22.2, U3.5 (+)
unnamed: C18.1, R23.2, R24.2, U3.3 (+)
unnamed: C19.1, R20.1
unnamed: C20.2, R21.2
unnamed: C21.1, R23.1
unnamed: D2.2 (A), R26.2
unnamed: D3.2 (A), R31.2
unnamed: IC1.7 ((PCINT6/XTAL1/TOSC1)PB6), R6.1, Y1.3
unnamed: IC1.8 ((PCINT7/XTAL2/TOSC2)PB7), R5.2
unnamed: IC1.12 ((PCINT0/CLKO/ICP1)PB0), R4.1
unnamed: IC1.30 ((PCINT16/RXD)PD0), P4.2, R13.1
unnamed: IC1.31 ((PCINT17/TXD)PD1), P4.1, R14.1
unnamed: J1.1, U2.2 (ANT)
unnamed: J2.1, U2.4 (TMS/GPIO19)
unnamed: J3.1, U2.5 (TCK/GPIO18)
unnamed: J4.1, U2.6 (TDO/GPIO21)
unnamed: J5.1, U2.7 (TDI/GPIO20)
unnamed: P1.9, R1.1
unnamed: P1.12, R2.1
unnamed: R3.1, U5.2 (RESET)
unnamed: R5.1, R6.2, Y1.1
unnamed: R7.1, U4.2 (RESET)
RX: R14.2, R19.1, U2.11 (RX/GPIO1)
TX: R13.2, U2.10 (TX/GPIO0)
